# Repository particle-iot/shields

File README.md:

# Shields for the Particle devices

You'll find here the hardware design files for shields for the Particle Electron, Photon and Core.

## License
Designed by Particle. Unless otherwise noted these files are distributed under a Creative Commons Attribution, Share-Alike license. Check LICENSE for more information.

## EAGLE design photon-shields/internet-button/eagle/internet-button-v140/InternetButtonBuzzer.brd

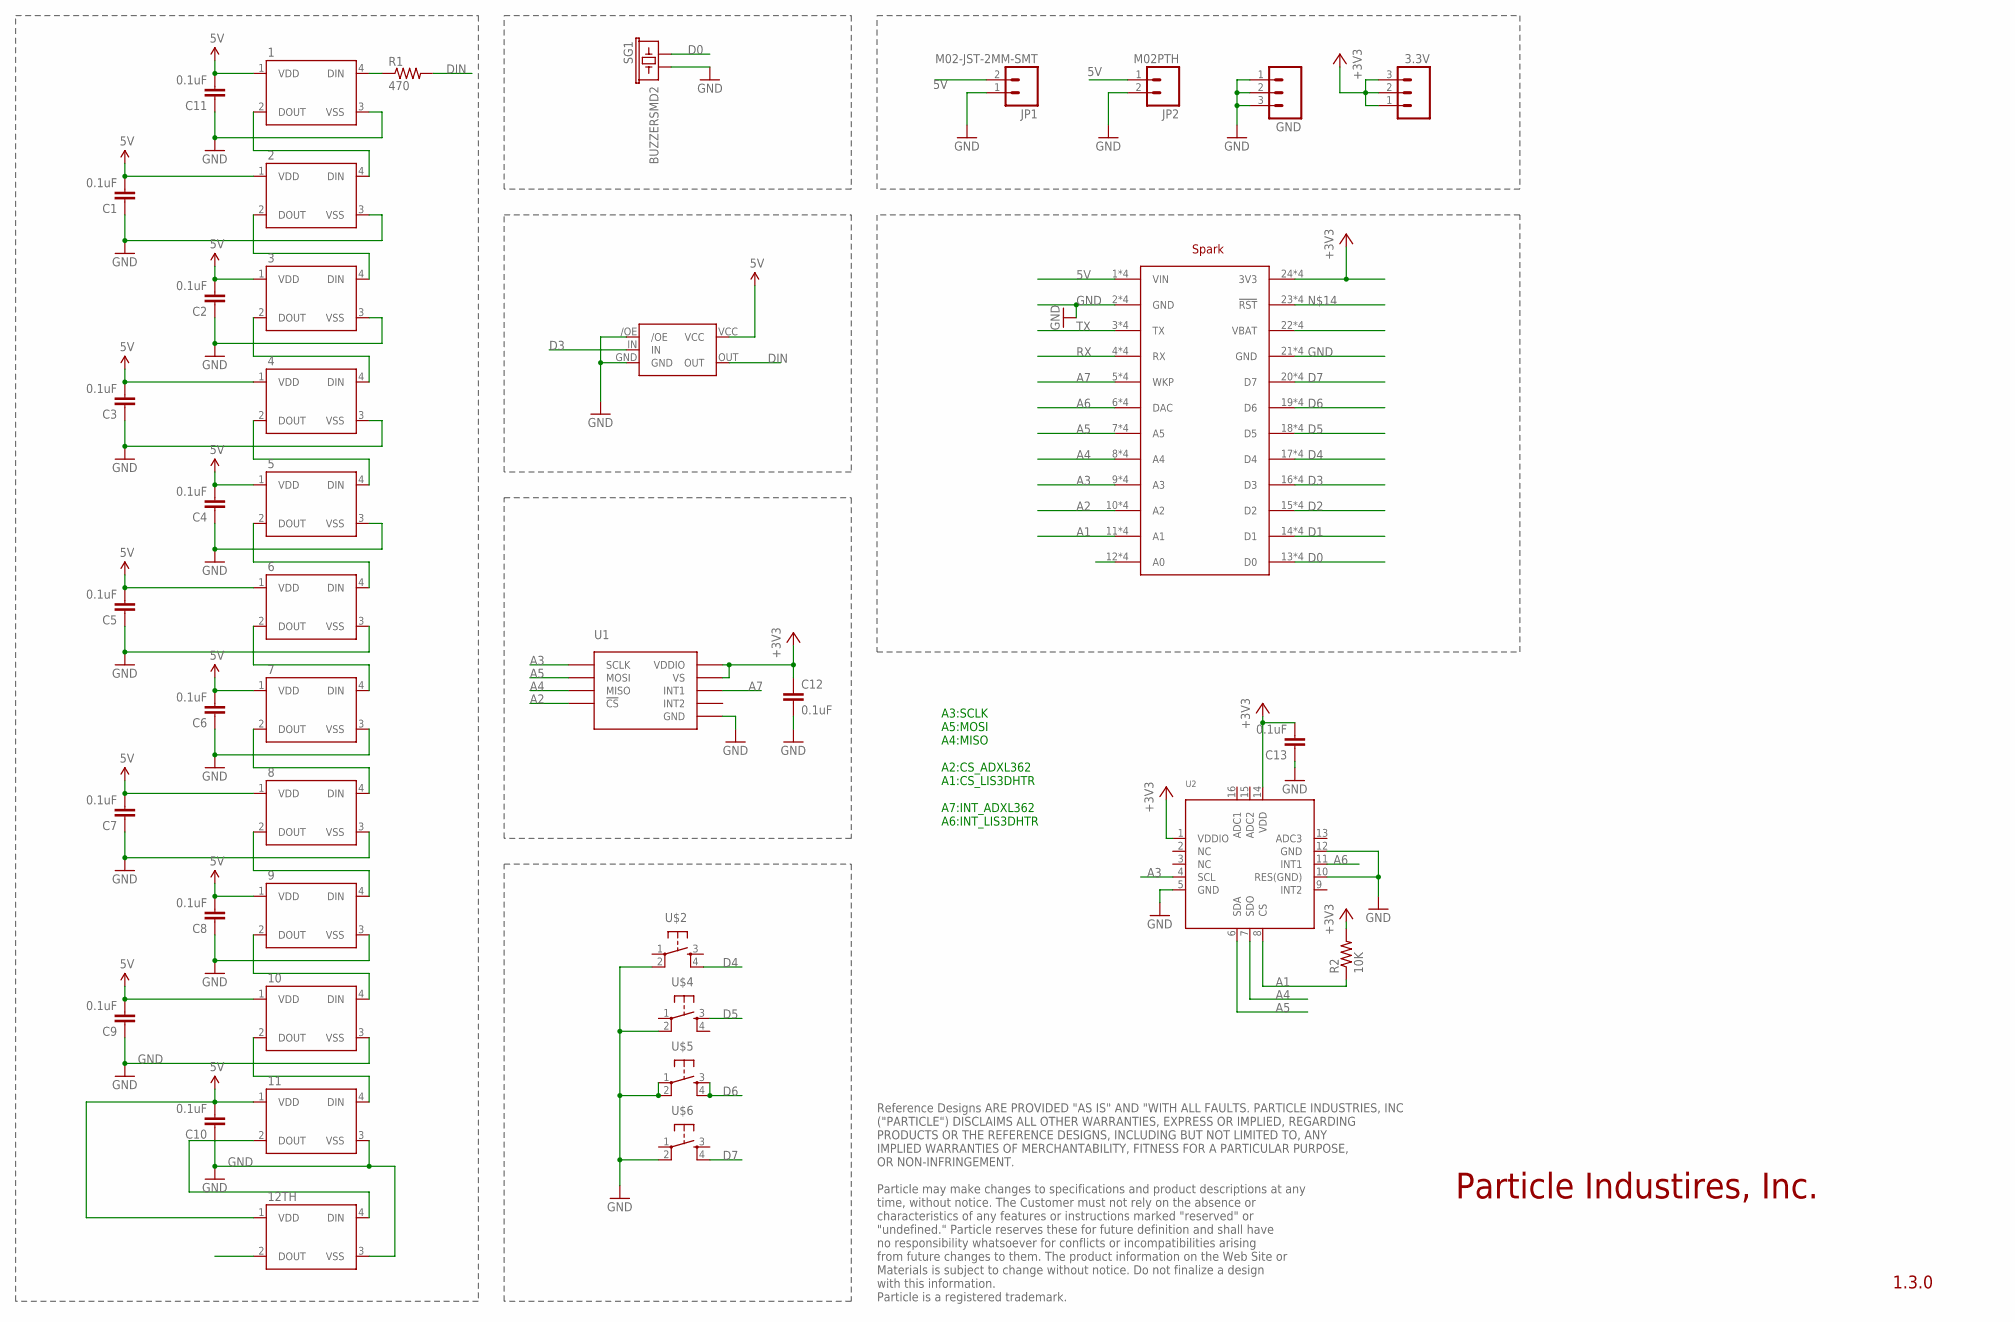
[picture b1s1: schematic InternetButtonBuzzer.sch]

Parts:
1, 2, 3, 4, 5, 6, 7, 8, 9, 10, 11: WS2812B
3.3V: M03LOCK_NO_SILK; 1X03_LOCK_NO_SILK
12TH: WS2812B; NOCREAM_WS2812B
C1, C2, C3, C4, C5, C6, C7, C8, C9, C10, C11, C12, C13: 0.1uF; 0603-CAP
GND: M03LOCK_NO_SILK; 1X03_LOCK_NO_SILK
JP1: M02-JST-2MM-SMT; JST-2-SMD
JP2: M02PTH; 1X02
R1: 470; 0603-RES
R2: 10K; 0603-RES
SG1: BUZZERSMD2; BUZZER-CCV
U1: ADXL362ADXL362-1:1; ADXL362-1:1
U2: ACCEL_LIS3DHTR; LGA16_3X3MM
U$2, U$4, U$5, U$6: 12MM_TACTILE_SWITCH
U$3: SPARK_LOGO_WITH_PLANE; SPARK_LOGO_PLUS_PLANE
U$7: SPARK_COREDUAL_HEADER; SPARK_CORE_DUAL_HEADER
U$8: NL17SZ125SOT553; SOT-553

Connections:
5V: 1.1 (VDD), 2.1 (VDD), 3.1 (VDD), 4.1 (VDD), 5.1 (VDD), 6.1 (VDD), 7.1 (VDD), 8.1 (VDD), 9.1 (VDD), 10.1 (VDD), 11.1 (VDD), 12TH.1 (VDD), C1.2, C2.2, C3.2, C4.2, C5.2, C6.2, C7.2, C8.2, C9.2, C10.2, C11.2, JP1.2 (1), JP2.1, U$7.1 (VIN), U$7.1B (VIN), U$7.@1 (VIN), U$7.@1B (VIN), U$8.VCC
+3V3: 3.3V.1, 3.3V.2, 3.3V.3, C12.1, C13.2, R2.2, U1.P$1 (VDDIO), U1.P$14 (VS), U2.1 (VDDIO), U2.14 (VDD), U$7.24 (3V3), U$7.24B (3V3), U$7.@24 (3V3), U$7.@24B (3V3)
A1: R2.1, U2.8 (CS), U$7.11 (A1), U$7.11B (A1), U$7.@11 (A1), U$7.@11B (A1)
A2: U1.P$8 (!CS), U$7.10 (A2), U$7.10B (A2), U$7.@10 (A2), U$7.@10B (A2)
A3: U1.P$4 (SCLK), U2.4 (SCL), U$7.9 (A3), U$7.9B (A3), U$7.@9 (A3), U$7.@9B (A3)
A4: U1.P$7 (MISO), U2.7 (SDO), U$7.8 (A4), U$7.8B (A4), U$7.@8 (A4), U$7.@8B (A4)
A5: U1.P$6 (MOSI), U2.6 (SDA), U$7.7 (A5), U$7.7B (A5), U$7.@7 (A5), U$7.@7B (A5)
A6: U2.11 (INT1), U$7.6 (DAC), U$7.6B (DAC), U$7.@6 (DAC), U$7.@6B (DAC)
A7: U1.P$11 (INT1), U$7.5 (WKP), U$7.5B (WKP), U$7.@5 (WKP), U$7.@5B (WKP)
D0: SG1.+ (1), U$7.13 (D0), U$7.13B (D0), U$7.@13 (D0), U$7.@13B (D0)
D1: U$7.14 (D1), U$7.14B (D1), U$7.@14 (D1), U$7.@14B (D1)
D2: U$7.15 (D2), U$7.15B (D2), U$7.@15 (D2), U$7.@15B (D2)
D3: U$7.16 (D3), U$7.16B (D3), U$7.@16 (D3), U$7.@16B (D3), U$8.IN
D4: U$2.4, U$7.17 (D4), U$7.17B (D4), U$7.@17 (D4), U$7.@17B (D4)
D5: U$4.3, U$7.18 (D5), U$7.18B (D5), U$7.@18 (D5), U$7.@18B (D5)
D6: U$5.3, U$5.4, U$7.19 (D6), U$7.19B (D6), U$7.@19 (D6), U$7.@19B (D6)
D7: U$6.4, U$7.20 (D7), U$7.20B (D7), U$7.@20 (D7), U$7.@20B (D7)
DIN: R1.2, U$8.OUT
GND: 1.3 (VSS), 2.3 (VSS), 3.3 (VSS), 4.3 (VSS), 5.3 (VSS), 6.3 (VSS), 7.3 (VSS), 8.3 (VSS), 9.3 (VSS), 10.3 (VSS), 11.3 (VSS), 12TH.3 (VSS), C1.1, C2.1, C3.1, C4.1, C5.1, C6.1, C7.1, C8.1, C9.1, C10.1, C11.1, C12.2, C13.1, GND.1, GND.2, GND.3, JP1.1 (2), JP2.2, SG1.- (2), U1.P$12 (GND), U1.P$13 (GND), U1.P$16 (GND), U2.5 (GND), U2.10 (RES(GND)), U2.12 (GND), U$2.2, U$4.2, U$5.1, U$5.2, U$6.2, U$7.2 (GND), U$7.2B (GND), U$7.21 (GND), U$7.21B (GND), U$7.@2 (GND), U$7.@2B (GND), U$7.@21 (GND), U$7.@21B (GND), U$8./OE, U$8.GND
unnamed: 2.2 (DOUT), 3.4 (DIN)
unnamed: 3.2 (DOUT), 4.4 (DIN)
unnamed: U$7.12 (A0), U$7.12B (A0), U$7.@12 (A0), U$7.@12B (A0)
unnamed: 11.2 (DOUT), 12TH.4 (DIN)
unnamed: 7.2 (DOUT), 8.4 (DIN)
unnamed: 8.2 (DOUT), 9.4 (DIN)
unnamed: 9.2 (DOUT), 10.4 (DIN)
unnamed: 10.2 (DOUT), 11.4 (DIN)
unnamed: U$7.23 (!RST), U$7.23B (!RST), U$7.@23 (!RST), U$7.@23B (!RST)
unnamed: U$7.22 (VBAT), U$7.22B (VBAT), U$7.@22 (VBAT), U$7.@22B (VBAT)
unnamed: 1.4 (DIN), R1.1
unnamed: 4.2 (DOUT), 5.4 (DIN)
unnamed: 5.2 (DOUT), 6.4 (DIN)
unnamed: 6.2 (DOUT), 7.4 (DIN)
unnamed: 1.2 (DOUT), 2.4 (DIN)
RX: U$7.4 (RX), U$7.4B (RX), U$7.@4 (RX), U$7.@4B (RX)
TX: U$7.3 (TX), U$7.3B (TX), U$7.@3 (TX), U$7.@3B (TX)

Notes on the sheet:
Reference Designs ARE PROVIDED "AS IS" AND "WITH ALL FAULTS. PARTICLE INDUSTRIES, INC ("PARTICLE") DISCLAIMS ALL OTHER WARRANTIES, EXPRESS OR IMPLIED, REGARDING PRODUCTS OR THE REFERENCE DESIGNS, INCLUDING BUT NOT LIMITED TO, ANY IMPLIED WARRANTIES OF MERCHANTABILITY, FITNESS FOR A PARTICULAR PURPO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
1.3.0
Particle Industires, Inc.
A3:SCLK A5:MOSI A4:MISO A2:CS_ADXL362 A1:CS_LIS3DHTR A7:INT_ADXL362 A6:INT_LIS3DHTR

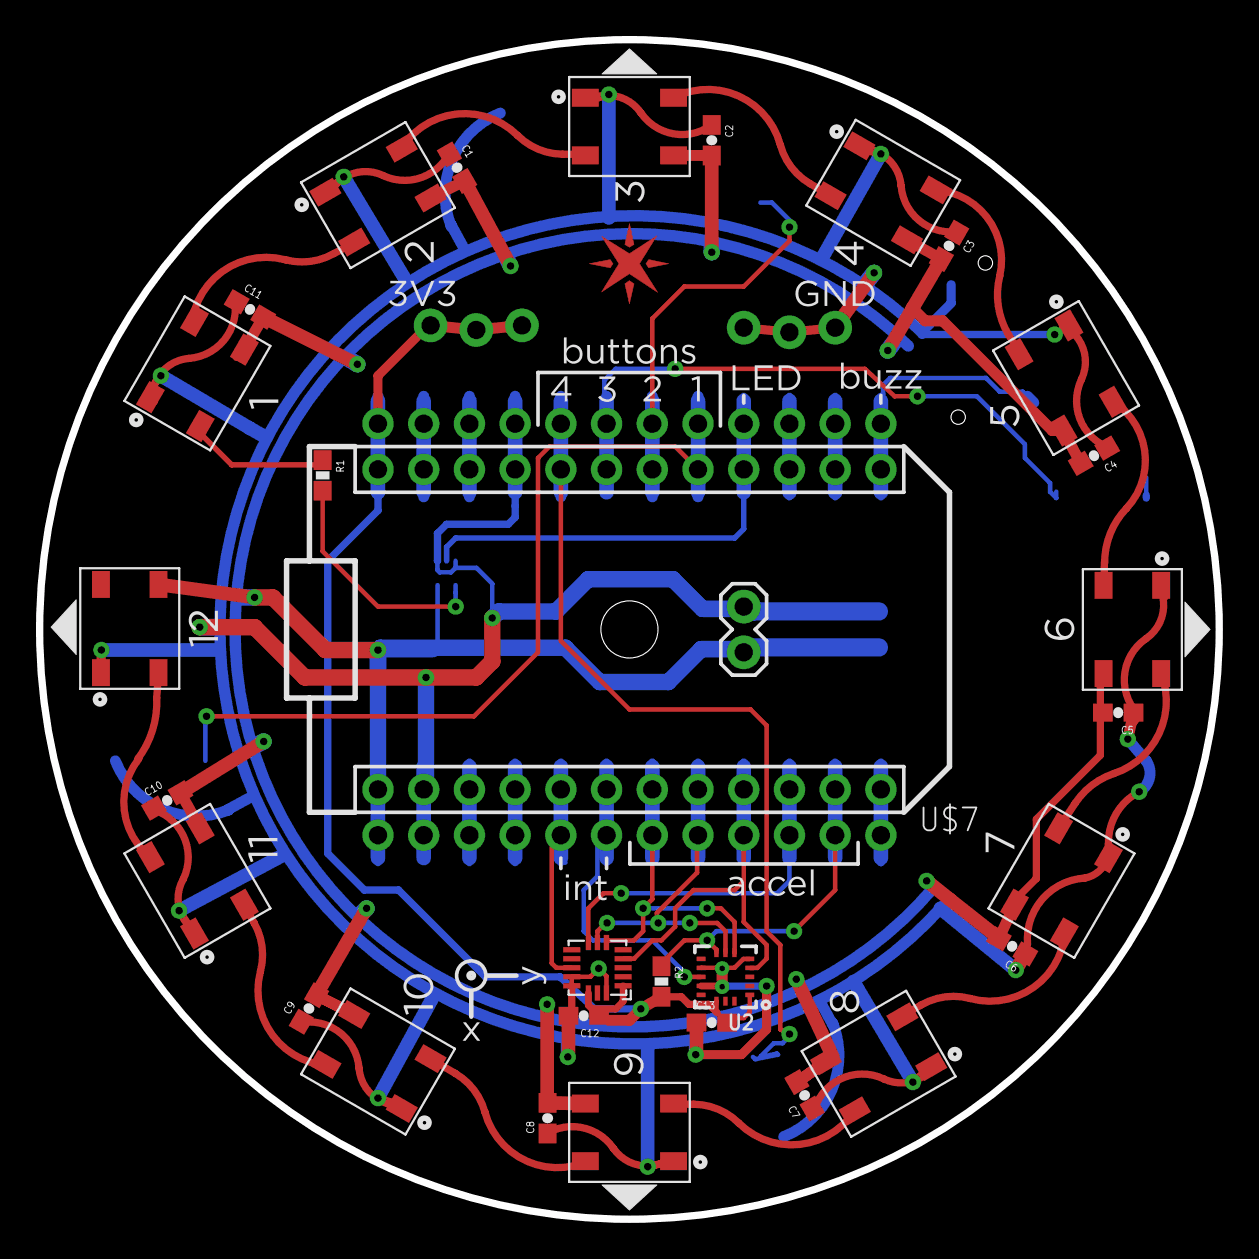
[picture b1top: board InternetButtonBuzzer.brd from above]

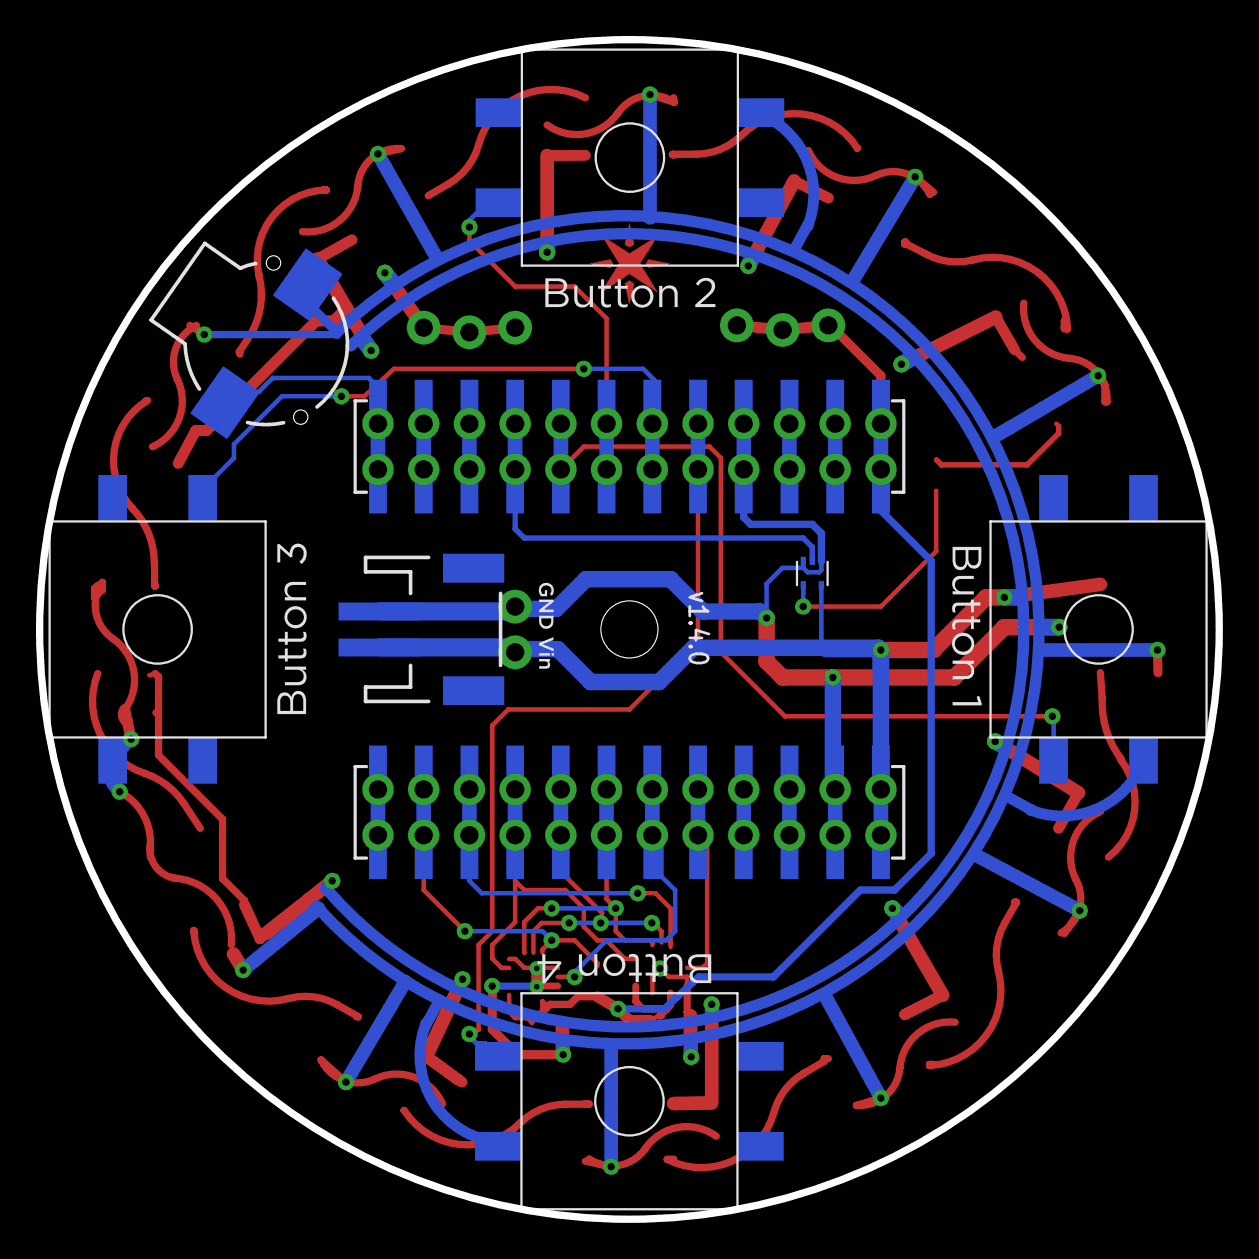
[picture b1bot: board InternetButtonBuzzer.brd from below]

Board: 2 copper layers, 65.5 x 65.5 mm, 41 parts (7 on the bottom side), 36 nets.

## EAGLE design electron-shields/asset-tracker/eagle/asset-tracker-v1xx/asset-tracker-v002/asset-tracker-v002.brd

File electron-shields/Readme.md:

# Electron Shields

* Asset tracker shield
* Solar shield

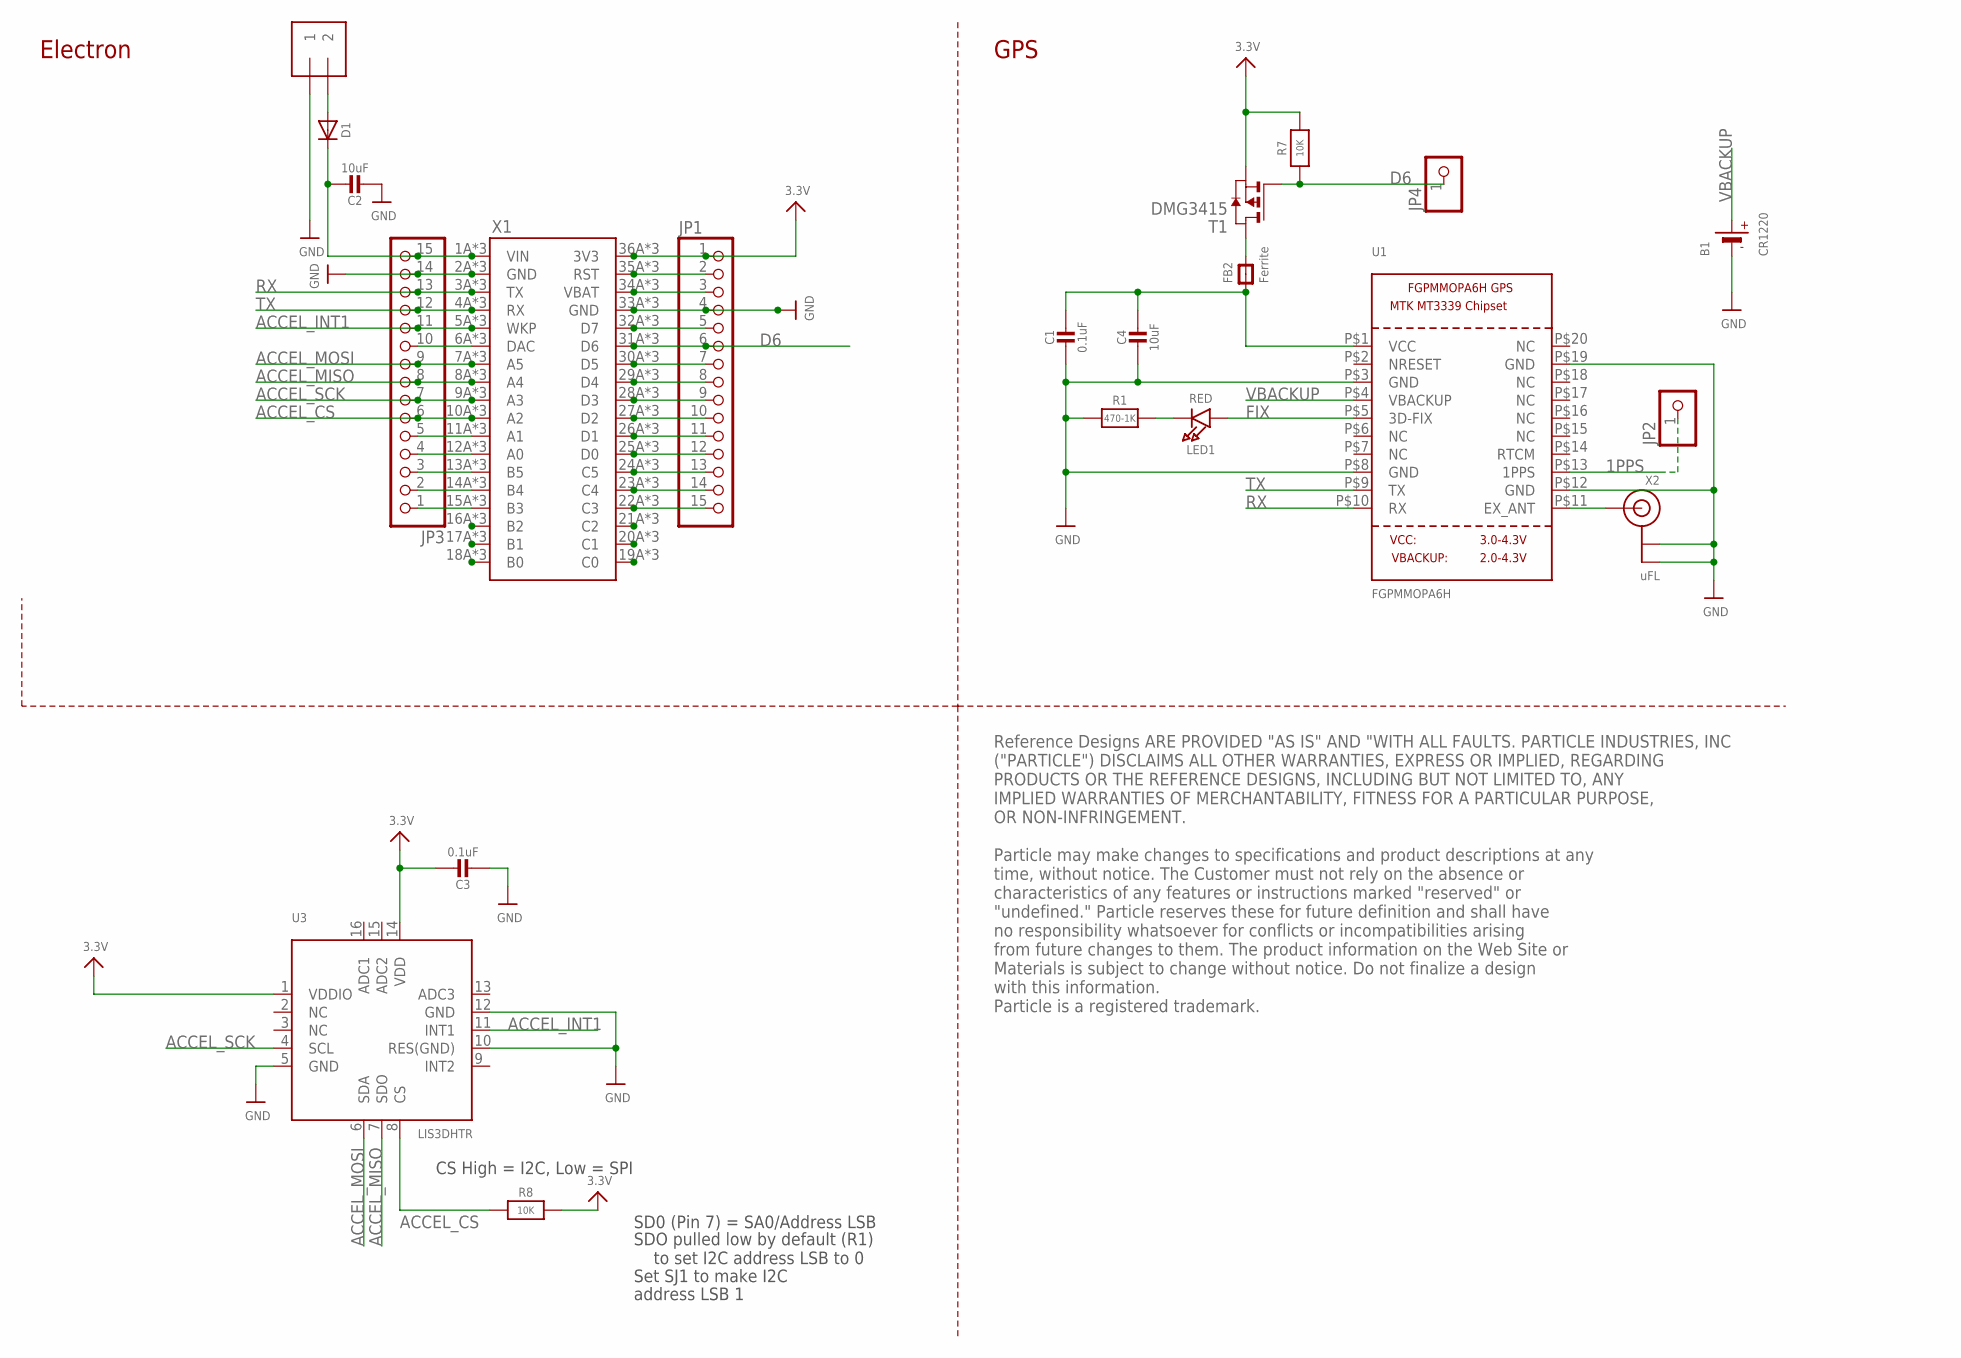
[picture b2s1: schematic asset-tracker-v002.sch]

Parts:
B1: CR1220
C1: 0.1uF; 0805-NO@1
C2, C4: 10uF; 0805-NO@1
C3: 0.1uF; 0805_10MGAP
D1: DIODESMA; SMADIODE
FB2: Ferrite; 0805-NO@1
J1: 1X2-3.5MM
JP1, JP3: HEADER-1X15; 1X15_ROUND_70
JP2, JP4: HEADER-1X1ROUND; 1X01_ROUND
LED1: RED; CHIPLED_0805_NOOUTLINE
R1: 470-1K; 0805-NO
R7, R8: 10K; 0805-NO
T1: DMG3415; SOT-23
U1: FGPMMOPA6H
U3: LIS3DHTR; LGA16_3X3MM
X1: ELECTRON; ELECTRON_SMT
X2: uFL; U.FL

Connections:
1PPS: JP2.1, U1.P$13 (1PPS)
3.3V: C3.1, JP1.1, R7.2, R8.2, T1.2 (S), U3.1 (VDDIO), U3.14 (VDD), X1.36A (3V3), X1.36B (3V3), X1.36C (3V3)
A0: JP3.4, X1.12A (A0), X1.12B (A0), X1.12C (A0)
A1: JP3.5, X1.11A (A1), X1.11B (A1), X1.11C (A1)
ACCEL_CS: JP3.6, R8.1, U3.8 (CS), X1.10A (A2), X1.10B (A2), X1.10C (A2)
ACCEL_INT1: JP3.11, U3.11 (INT1), X1.5A (WKP), X1.5B (WKP), X1.5C (WKP)
ACCEL_MISO: JP3.8, U3.7 (SDO), X1.8A (A4), X1.8B (A4), X1.8C (A4)
ACCEL_MOSI: JP3.9, U3.6 (SDA), X1.7A (A5), X1.7B (A5), X1.7C (A5)
ACCEL_SCK: JP3.7, U3.4 (SCL), X1.9A (A3), X1.9B (A3), X1.9C (A3)
B3: JP3.1, X1.15A (B3), X1.15B (B3), X1.15C (B3)
B4: JP3.2, X1.14A (B4), X1.14B (B4), X1.14C (B4)
B5: JP3.3, X1.13A (B5), X1.13B (B5), X1.13C (B5)
C3: JP1.15, X1.22A (C3), X1.22B (C3), X1.22C (C3)
C4: JP1.14, X1.23A (C4), X1.23B (C4), X1.23C (C4)
C5: JP1.13, X1.24A (C5), X1.24B (C5), X1.24C (C5)
D0: JP1.12, X1.25A (D0), X1.25B (D0), X1.25C (D0)
D1: JP1.11, X1.26A (D1), X1.26B (D1), X1.26C (D1)
D2: JP1.10, X1.27A (D2), X1.27B (D2), X1.27C (D2)
D3: JP1.9, X1.28A (D3), X1.28B (D3), X1.28C (D3)
D4: JP1.8, X1.29A (D4), X1.29B (D4), X1.29C (D4)
D5: JP1.7, X1.30A (D5), X1.30B (D5), X1.30C (D5)
D6: JP1.6, JP4.1, R7.1, T1.3 (G), X1.31A (D6), X1.31B (D6), X1.31C (D6)
D7: JP1.5, X1.32A (D7), X1.32B (D7), X1.32C (D7)
DAC: JP3.10, X1.6A (DAC), X1.6B (DAC), X1.6C (DAC)
FIX: LED1.A, U1.P$5 (3D-FIX)
GND: B1.-, C1.2, C2.2, C3.2, C4.2, J1.1, JP1.4, JP3.14, R1.1, U1.P$3 (GND), U1.P$8 (GND), U1.P$12 (GND), U1.P$19 (GND), U3.5 (GND), U3.10 (RES(GND)), U3.12 (GND), X1.2A (GND), X1.2B (GND), X1.2C (GND), X1.33A (GND), X1.33B (GND), X1.33C (GND), X2.1 (GND), X2.2 (GND)
unnamed: C1.1, C4.1, FB2.1, U1.P$1 (VCC)
unnamed: LED1.C, R1.2
unnamed: U1.P$11 (EX_ANT), X2.3 (SIGNAL)
unnamed: C2.1, D1.C, JP3.15, X1.1A (VIN), X1.1B (VIN), X1.1C (VIN)
unnamed: D1.A, J1.2
unnamed: X1.16A (B2), X1.16B (B2), X1.16C (B2)
unnamed: X1.17A (B1), X1.17B (B1), X1.17C (B1)
unnamed: X1.18A (B0), X1.18B (B0), X1.18C (B0)
unnamed: X1.21A (C2), X1.21B (C2), X1.21C (C2)
unnamed: X1.20A (C1), X1.20B (C1), X1.20C (C1)
unnamed: X1.19A (C0), X1.19B (C0), X1.19C (C0)
RST: JP1.2, X1.35A (RST), X1.35B (RST), X1.35C (RST)
RX: JP3.13, U1.P$10 (RX), X1.3A (TX), X1.3B (TX), X1.3C (TX)
TX: JP3.12, U1.P$9 (TX), X1.4A (RX), X1.4B (RX), X1.4C (RX)
VBACKUP: B1.+$1 (+), U1.P$4 (VBACKUP)
VBAT: JP1.3, X1.34A (VBAT), X1.34B (VBAT), X1.34C (VBAT)
VCC: FB2.2, T1.1 (D)

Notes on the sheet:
SD0 (Pin 7) = SA0/Address LSB
CS High = I2C, Low = SPI
SDO pulled low by default (R1) to set I2C address LSB to 0
Set SJ1 to make I2C
address LSB 1
GPS
Electron
Reference Designs ARE PROVIDED "AS IS" AND "WITH ALL FAULTS. PARTICLE INDUSTRIES, INC ("PARTICLE") DISCLAIMS ALL OTHER WARRANTIES, EXPRESS OR IMPLIED, REGARDING PRODUCTS OR THE REFERENCE DESIGNS, INCLUDING BUT NOT LIMITED TO, ANY IMPLIED WARRANTIES OF MERCHANTABILITY, FITNESS FOR A PARTICULAR PURPO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

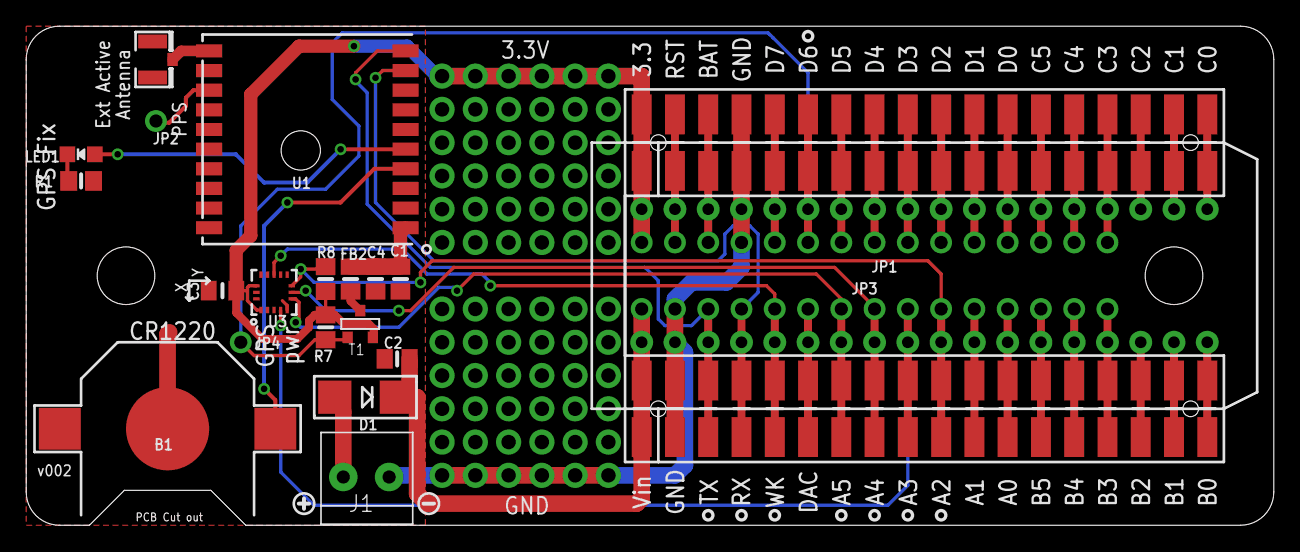
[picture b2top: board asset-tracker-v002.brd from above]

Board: 2 copper layers, 95.2 x 38.1 mm, 23 parts (0 on the bottom side), 43 nets.

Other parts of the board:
U$13: SYMBOL_MINUS
U$21: SYMBOL_PLUS

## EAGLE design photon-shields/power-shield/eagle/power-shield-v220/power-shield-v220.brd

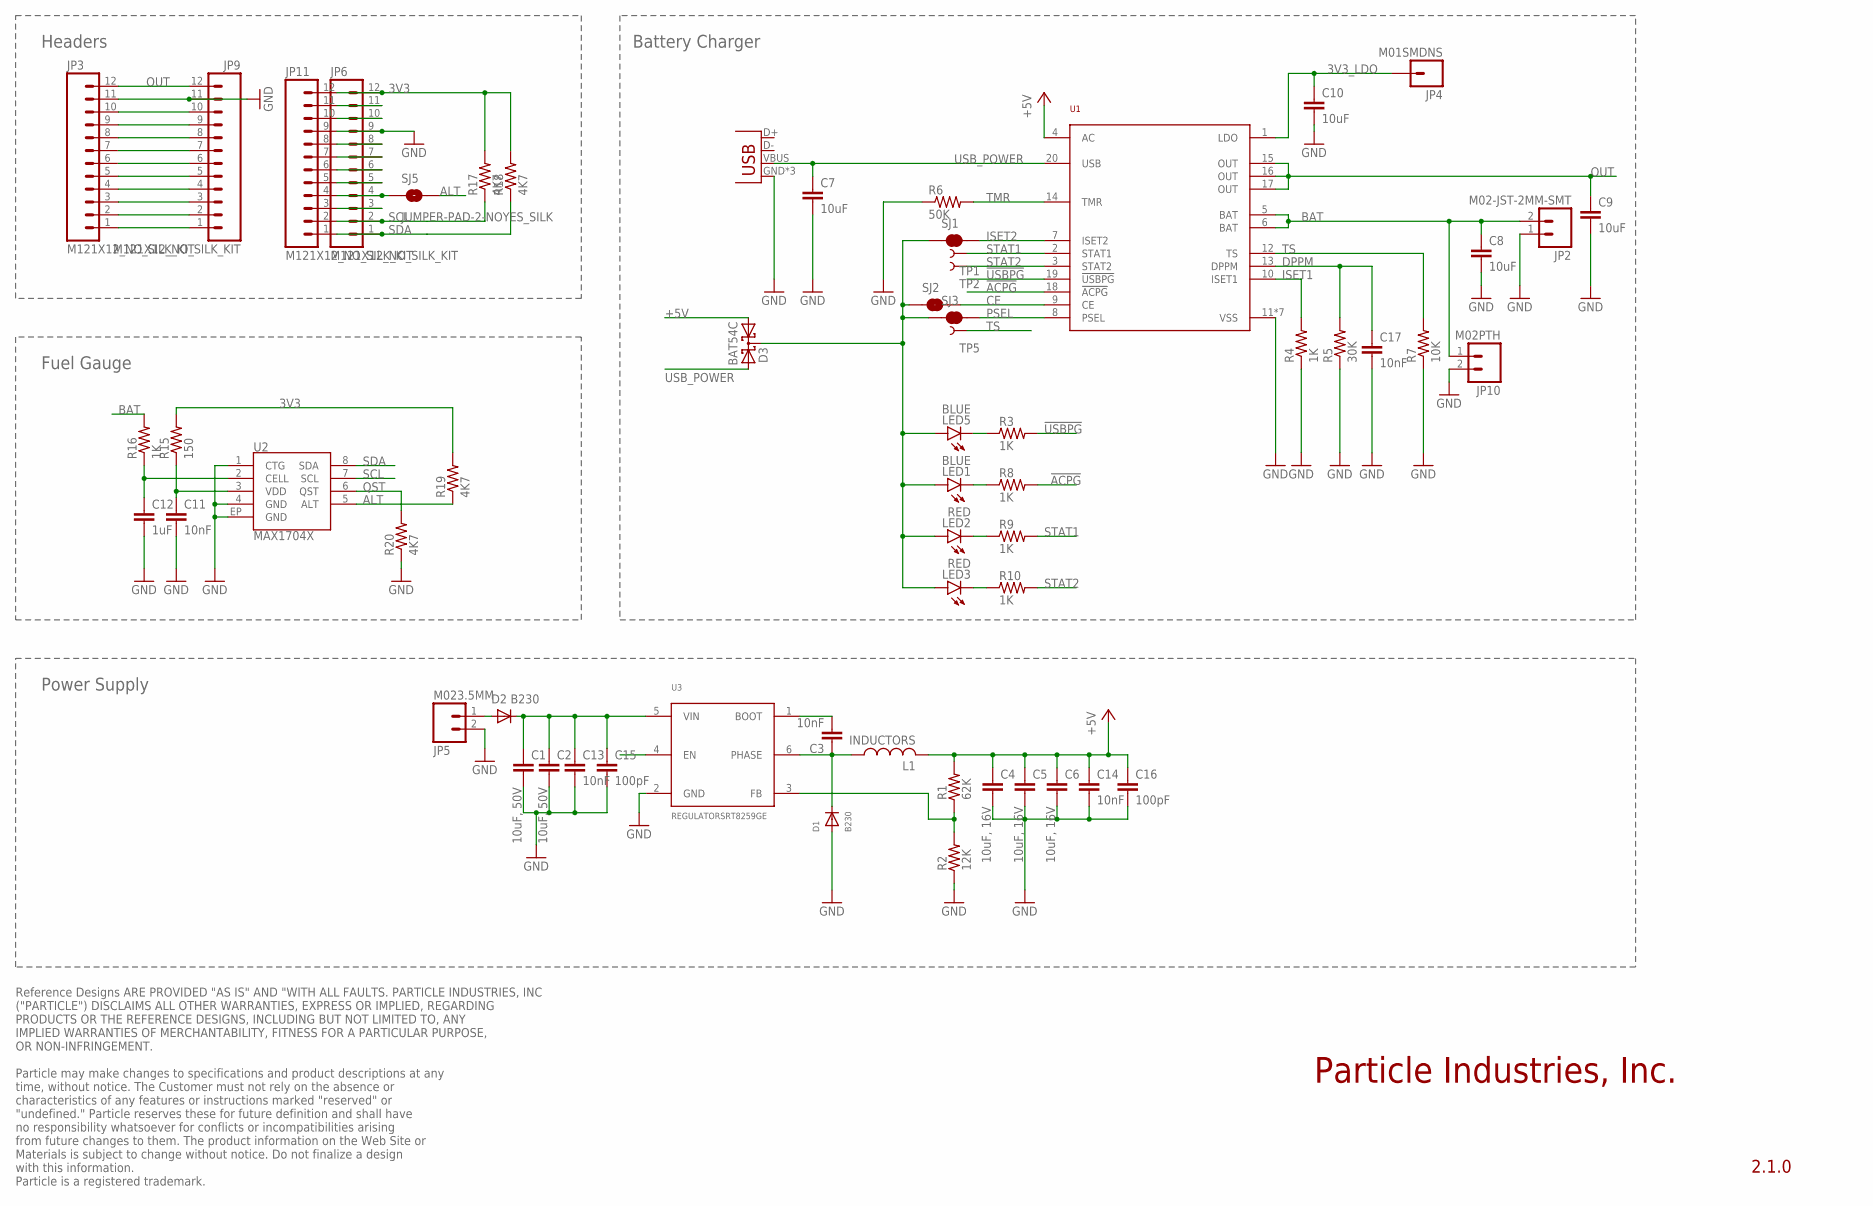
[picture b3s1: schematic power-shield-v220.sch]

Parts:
C1, C2: 10uF, 50V; 1206
C3, C11, C13, C14, C17: 10nF; 0402-CAP
C4, C5, C6: 10uF, 16V; 1206
C7, C8, C9, C10: 10uF; 0603-CAP
C12: 1uF; 0402-CAP
C15, C16: 100pF; 0402-CAP
D1, D2: B230; SMADIODE
D3: BAT54C; SOT23
JP1: USBUSB-MICROB-SLOT-HOLE; USB-MICROB-SLOT-HOLE
JP2: M02-JST-2MM-SMT; JST-2-SMD
JP3, JP6, JP9, JP11: M121X12_NO_SILK_KIT; 1X12_NO_SILK_KIT
JP4: M01SMDNS; 1X01NS
JP5: M023.5MM; SCREWTERMINAL-3.5MM-2
JP10: M02PTH; 1X02
L1: INDUCTORS; NR8040T6R8N
LED1, LED5: BLUE; LED-0603
LED2, LED3: RED; LED-0603
R1: 62K; 0603-RES
R2: 12K; 0603-RES
R3, R4, R8, R9, R10: 1K; 0402-RES
R5: 30K; 0402-RES
R6: 50K; 0402-RES
R7: 10K; 0402-RES
R15: 150; 0603-RES
R16: 1K; 0603-RES
R17, R18, R19, R20: 4K7; 0402-RES
SJ1, SJ2, SJ3: JUMPER-PAD-2-NC_BY_TRACE; PAD-JUMPER-2-NC_BY_TRACE_YES_SILK
SJ5: JUMPER-PAD-2-NOYES_SILK; PAD-JUMPER-2-NO_YES_SILK
TP1, TP2, TP5: TEST-POINT3; PAD.03X.03
U1: BQ24030BQ24030; R-PVQFN-N20
U2: MAX1704X; TDFN-8
U3: REGULATORSRT8259GE; SOT23-6

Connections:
3V3: JP6.12, JP11.12, R15.2, R17.2, R18.2, R19.2
3V3_LDO: C10.1, JP4.1, U1.1 (LDO)
!ACPG: R8.2, U1.18 (!ACPG)
!USBPG: R3.2, U1.19 (!USBPG)
+5V: C4.1, C5.1, C6.1, C14.1, C16.1, D3.1 (A1), L1.P$2 (2), R1.2, U1.4 (AC)
ALT: R19.1, SJ5.2, U2.5 (ALT)
BAT: C8.1, JP2.2 (1), JP10.1, R16.2, U1.5 (BAT), U1.6 (BAT)
CE: SJ2.2, U1.9 (CE)
DPPM: C17.1, R5.2, U1.13 (DPPM)
GND: C1.2, C2.2, C4.2, C5.2, C6.2, C7.2, C8.2, C9.2, C10.2, C11.2, C12.2, C13.2, C14.2, C15.2, C16.2, C17.2, D1.A, JP1.GND, JP1.MT1 (GND), JP1.MT2 (GND), JP2.1 (2), JP3.11, JP5.2, JP6.9, JP9.11, JP10.2, JP11.9, R2.1, R4.1, R5.1, R6.1, R7.1, R20.1, U1.11 (VSS), U1.21 (VSS), U1.22 (VSS), U1.23 (VSS), U1.24 (VSS), U1.25 (VSS), U1.26 (VSS), U2.1 (CTG), U2.4 (GND), U2.EP (GND), U3.2 (GND)
ISET1: R4.2, U1.10 (ISET1)
ISET2: SJ1.2, U1.7 (ISET2)
unnamed: LED5.C, R3.1
unnamed: D3.3 (CC), LED1.A, LED2.A, LED3.A, LED5.A, SJ1.1, SJ2.1, SJ3.1
unnamed: LED3.C, R10.1
unnamed: LED2.C, R9.1
unnamed: LED1.C, R8.1
unnamed: JP6.4, JP11.4, SJ5.1
unnamed: JP3.1, JP9.1
unnamed: JP3.2, JP9.2
unnamed: JP3.3, JP9.3
unnamed: C12.1, R16.1, U2.2 (CELL)
unnamed: C11.1, R15.1, U2.3 (VDD)
unnamed: JP3.4, JP9.4
unnamed: C1.1, C2.1, C13.1, C15.1, D2.C, U3.5 (VIN)
unnamed: JP3.5, JP9.5
unnamed: JP3.6, JP9.6
unnamed: JP3.7, JP9.7
unnamed: JP3.8, JP9.8
unnamed: JP3.9, JP9.9
unnamed: JP3.10, JP9.10
unnamed: JP6.11, JP11.11
unnamed: JP6.10, JP11.10
unnamed: JP6.8, JP11.8
unnamed: JP6.7, JP11.7
unnamed: JP6.6, JP11.6
unnamed: JP6.5, JP11.5
unnamed: JP6.3, JP11.3
unnamed: D2.A, JP5.1
unnamed: C3.1, D1.C, L1.P$1 (1), U3.6 (PHASE)
unnamed: C3.2, U3.1 (BOOT)
unnamed: R1.1, R2.2, U3.3 (FB)
OUT: C9.1, JP3.12, JP9.12, U1.15 (OUT), U1.16 (OUT), U1.17 (OUT)
PSEL: SJ3.2, U1.8 (PSEL)
QST: R20.2, U2.6 (QST)
SCL: JP6.2, JP11.2, R17.1, U2.7 (SCL)
SDA: JP6.1, JP11.1, R18.1, U2.8 (SDA)
STAT1: R9.2, TP1.P$1, U1.2 (STAT1)
STAT2: R10.2, TP2.P$1, U1.3 (STAT2)
TMR: R6.2, U1.14 (TMR)
TS: R7.2, TP5.P$1, U1.12 (TS)
USB_POWER: C7.1, D3.2 (A2), JP1.VBUS, U1.20 (USB)

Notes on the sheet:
Power Supply
Headers
Fuel Gauge
Battery Charger
Reference Designs ARE PROVIDED "AS IS" AND "WITH ALL FAULTS. PARTICLE INDUSTRIES, INC ("PARTICLE") DISCLAIMS ALL OTHER WARRANTIES, EXPRESS OR IMPLIED, REGARDING PRODUCTS OR THE REFERENCE DESIGNS, INCLUDING BUT NOT LIMITED TO, ANY IMPLIED WARRANTIES OF MERCHANTABILITY, FITNESS FOR A PARTICULAR PURPO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
2.1.0
Particle Industries, Inc.

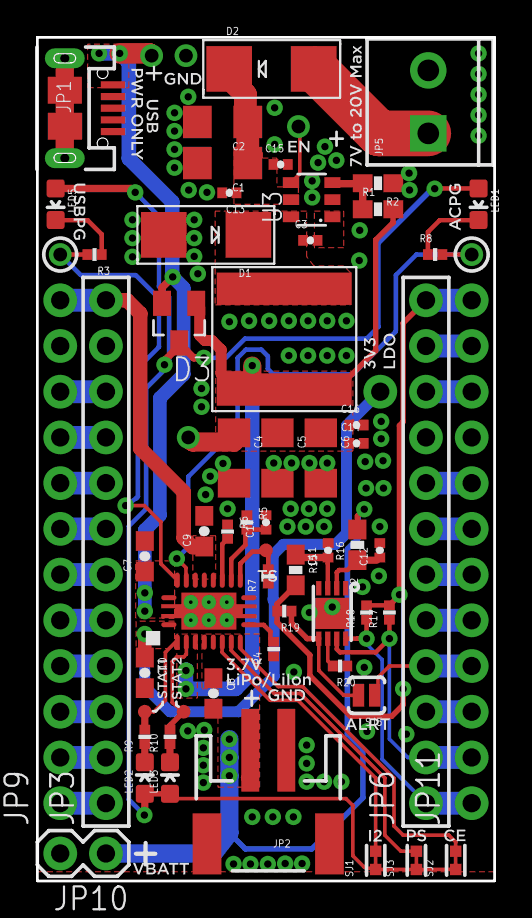
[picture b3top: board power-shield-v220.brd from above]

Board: 2 copper layers, 25.4 x 46.9 mm, 60 parts (0 on the bottom side), 52 nets.

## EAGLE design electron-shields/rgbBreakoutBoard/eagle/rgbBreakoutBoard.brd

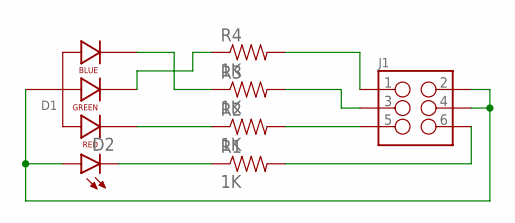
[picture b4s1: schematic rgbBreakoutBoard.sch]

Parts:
D1: LED-RGB-CA-THRUCLEAR; LED-RGB-THRU
D2: LED5MM
J1: M03X2SMT; 2X3_SMT_POSTS
R1, R2, R3, R4: 1K; 0603-RES

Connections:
unnamed: D2.K (C), R1.1
unnamed: D1.1 (RED_CATHODE), R2.1
unnamed: D1.4 (BLUE_CATHODE), R3.1
unnamed: D1.3 (GREEN_CATHODE), R4.1
unnamed: D1.2 (ANODE), D2.A, J1.2, J1.4
unnamed: J1.1, R4.2
unnamed: J1.3, R3.2
unnamed: J1.5, R2.2
unnamed: J1.6, R1.2

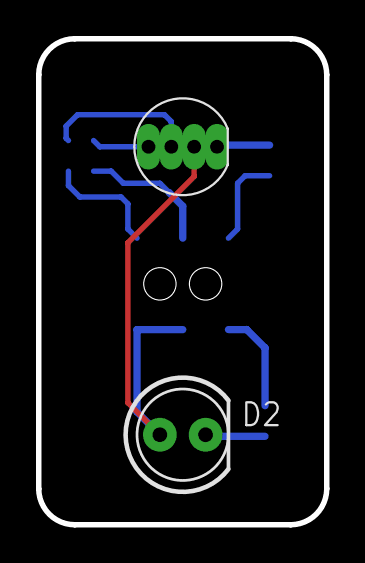
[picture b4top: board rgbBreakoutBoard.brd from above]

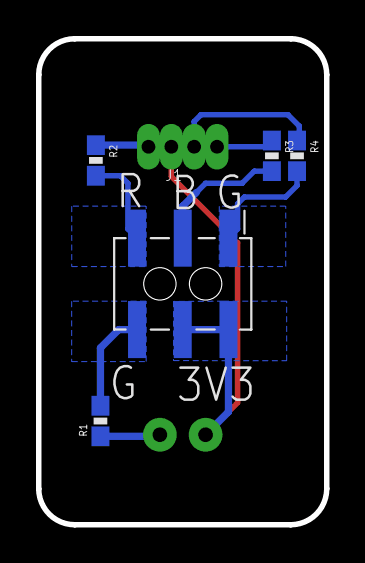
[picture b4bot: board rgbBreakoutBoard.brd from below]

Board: 2 copper layers, 16.0 x 27.0 mm, 7 parts (5 on the bottom side), 9 nets.

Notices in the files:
parts and their libraries:
SparkFun-DiscreteSemi: Licensing: Creative Commons ShareAlike 4.0 International - https://creativecommons.org/licenses/by-sa/4.0
SparkFun-Aesthetics: Licensing: CC v3.0 Share-Alike You are welcome to use this library for commercial purposes.
